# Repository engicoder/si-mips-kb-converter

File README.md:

View this project on [CADLAB.io](https://cadlab.io/project/24614). 

# si-mips-kb-converter
Mainboard replacement for SI version of mips 16-00100 keyboard to convert to USB

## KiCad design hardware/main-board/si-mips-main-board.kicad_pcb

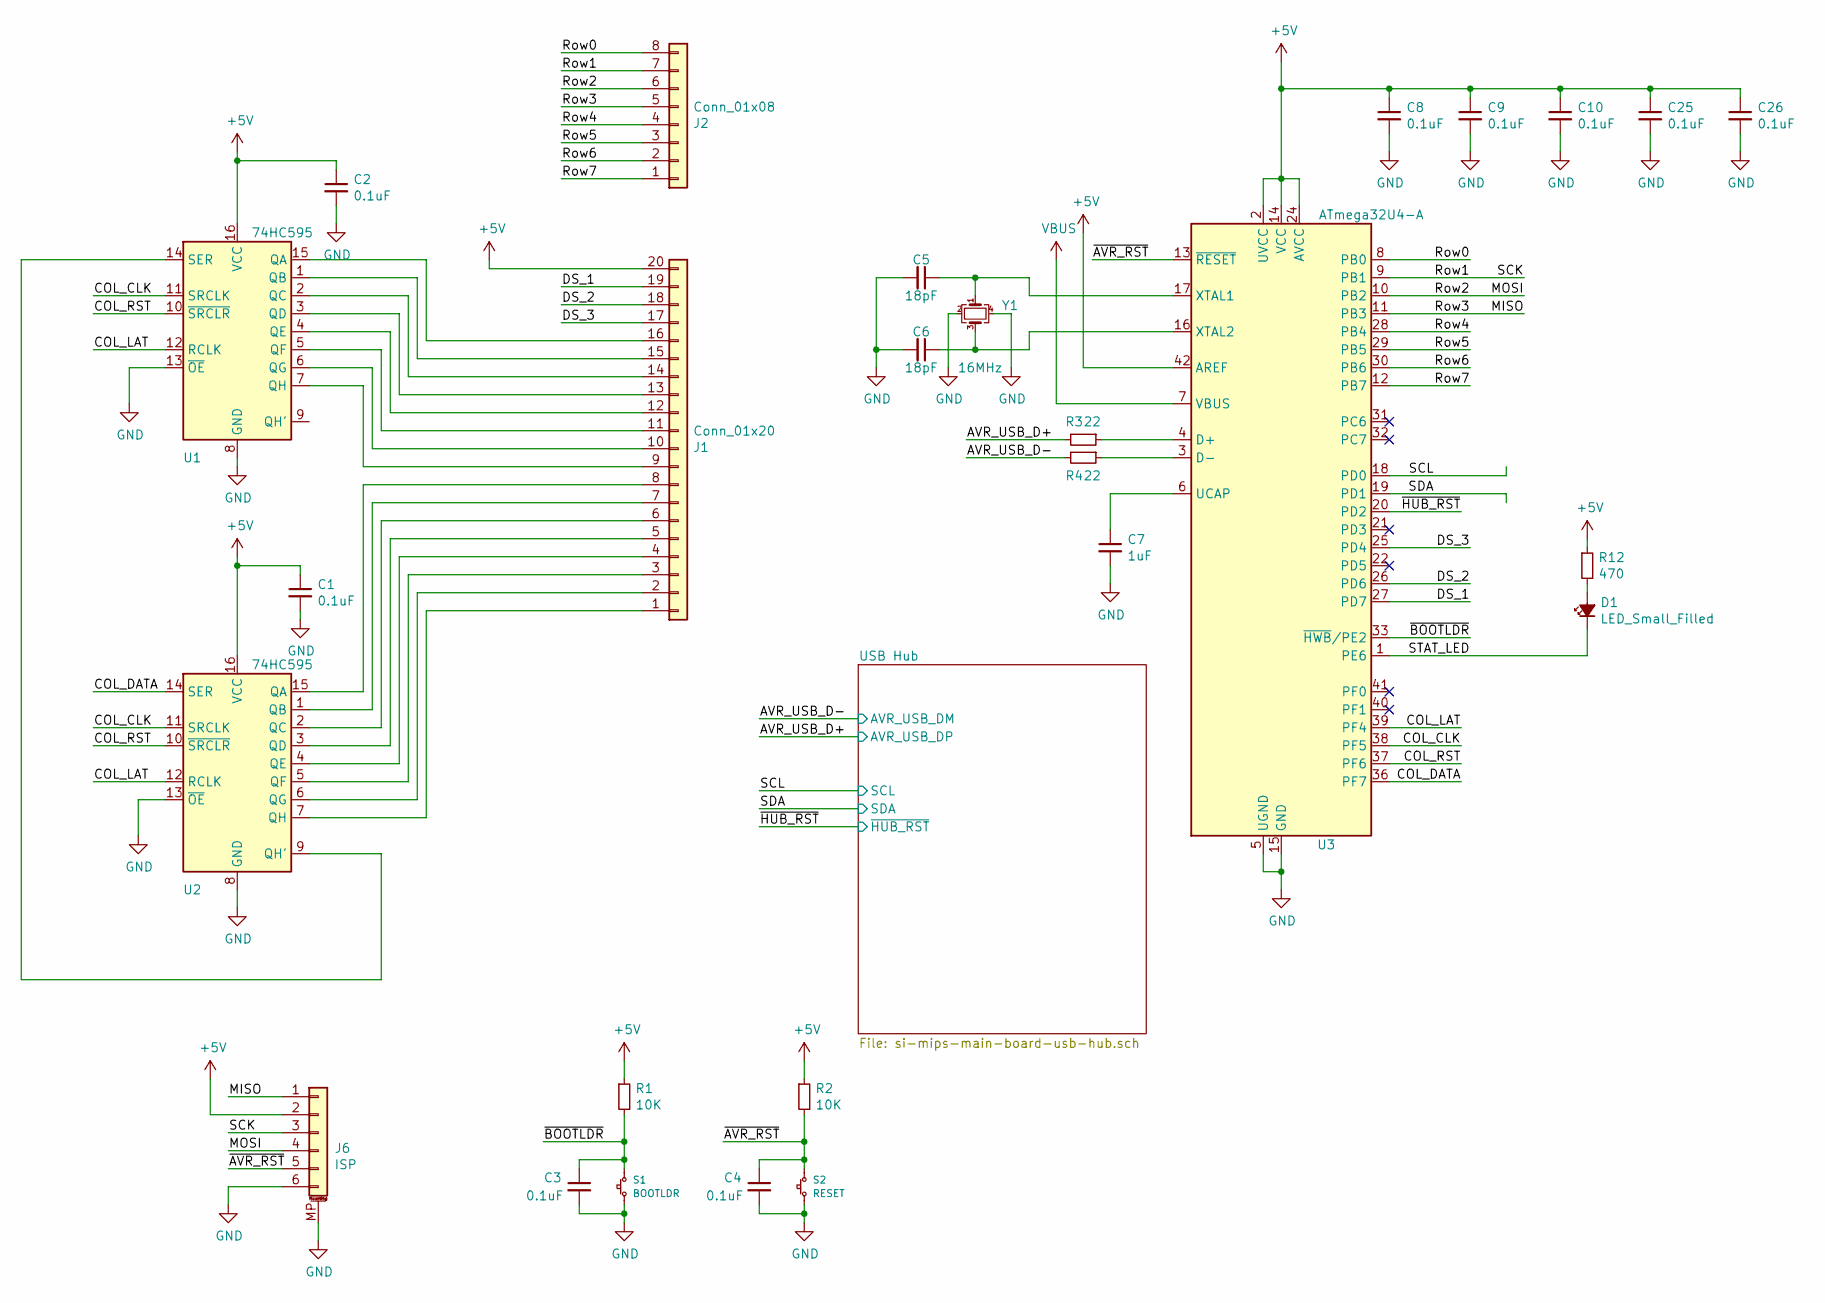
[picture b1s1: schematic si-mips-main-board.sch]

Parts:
C1, C2, C3, C4, C8, C9, C10, C25, C26: 0.1uF; C_0603_1608Metric
C5, C6: 18pF; C_0603_1608Metric
C7: 1uF; C_0603_1608Metric
D1: LED_Small_Filled; LED_0603_1608Metric
J1: Conn_01x20; PinHeader_1x20_P2.54mm_Vertical
J2: Conn_01x08; PinHeader_1x08_P2.54mm_Vertical
J6: ISP; JST_SH_SM06B-SRSS-TB_1x06-1MP_P1.00mm_Horizontal
R1, R2: 10K; R_0603_1608Metric
R3, R4: 22; R_0603_1608Metric
R12: 470; R_0603_1608Metric
S1: BOOTLDR; SW_SPST_Omron_B3FS-101xP
S2: RESET; SW_SPST_Omron_B3FS-101xP
U1, U2: 74HC595; SO-16_3.9x9.9mm_P1.27mm
U3: ATmega32U4-A; TQFP-44_10x10mm_P0.8mm
Y1: 16MHz; Crystal_SMD_3225-4Pin_3.2x2.5mm

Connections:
+5V: C1.1, C2.1, C8.1, C9.1, C10.1, C25.1, C26.1, J1.20, J6.2, R1.1, R2.1, R12.1, U1.16 (VCC), U2.16 (VCC), U3.2 (UVCC), U3.14 (VCC), U3.24 (AVCC), U3.34 (VCC), U3.42 (AREF), U3.44 (AVCC); also elsewhere on the board
/AVR_USB_D+: R3.2; also elsewhere on the board
/AVR_USB_D-: R4.2; also elsewhere on the board
/COL_CLK: U1.11 (SRCLK), U2.11 (SRCLK), U3.38 (PF5)
/COL_DATA: U2.14 (SER), U3.36 (PF7)
/COL_LAT: U1.12 (RCLK), U2.12 (RCLK), U3.39 (PF4)
/COL_RST: U1.10 (~SRCLR), U2.10 (~SRCLR), U3.37 (PF6)
/DS_1: J1.19, U3.27 (PD7)
/DS_2: J1.18, U3.26 (PD6)
/DS_3: J1.17, U3.25 (PD4)
/MISO: J2.5, J6.1, U3.11 (PB3)
/MOSI: J2.6, J6.4, U3.10 (PB2)
/Row0: J2.8, U3.8 (PB0)
/Row1: J2.7, J6.3, U3.9 (PB1)
/Row4: J2.4, U3.28 (PB4)
/Row5: J2.3, U3.29 (PB5)
/Row6: J2.2, U3.30 (PB6)
/Row7: J2.1, U3.12 (PB7)
/SCL: U3.18 (PD0); also elsewhere on the board
/SDA: U3.19 (PD1); also elsewhere on the board
/STAT_LED: D1.1 (K), U3.1 (PE6)
/~AVR_RST: C4.1, J6.5, R2.2, S2.1, U3.13 (~RESET)
/~BOOTLDR: C3.1, R1.2, S1.1, U3.33 (~HWB~/PE2)
/~HUB_RST: U3.20 (PD2); also elsewhere on the board
GND: C1.2, C2.2, C3.2, C4.2, C5.2, C6.2, C7.2, C8.2, C9.2, C10.2, C25.2, C26.2, J6.6, J6.MP (MountPin), S1.2, S2.2, U1.8 (GND), U1.13 (~OE), U2.8 (GND), U2.13 (~OE), U3.5 (UGND), U3.15 (GND), U3.23 (GND), U3.35 (GND), U3.43 (GND), Y1.2, Y1.4; also elsewhere on the board
unnamed: C5.1, U3.17 (XTAL1), Y1.1
unnamed: C6.1, U3.16 (XTAL2), Y1.3
unnamed: C7.1, U3.6 (UCAP)
unnamed: D1.2 (A), R12.2
unnamed: J1.1, U2.7 (QH)
unnamed: J1.2, U2.6 (QG)
unnamed: J1.3, U2.5 (QF)
unnamed: J1.4, U2.4 (QE)
unnamed: J1.5, U2.3 (QD)
unnamed: J1.6, U2.2 (QC)
unnamed: J1.7, U2.1 (QB)
unnamed: J1.8, U2.15 (QA)
unnamed: J1.9, U1.7 (QH)
unnamed: J1.10, U1.6 (QG)
unnamed: J1.11, U1.5 (QF)
unnamed: J1.12, U1.4 (QE)
unnamed: J1.13, U1.3 (QD)
unnamed: J1.14, U1.2 (QC)
unnamed: J1.15, U1.1 (QB)
unnamed: J1.16, U1.15 (QA)
unnamed: R3.1, U3.4 (D+)
unnamed: R4.1, U3.3 (D-)
unnamed: U1.14 (SER), U2.9 (QH')
VBUS: U3.7 (VBUS); also elsewhere on the board

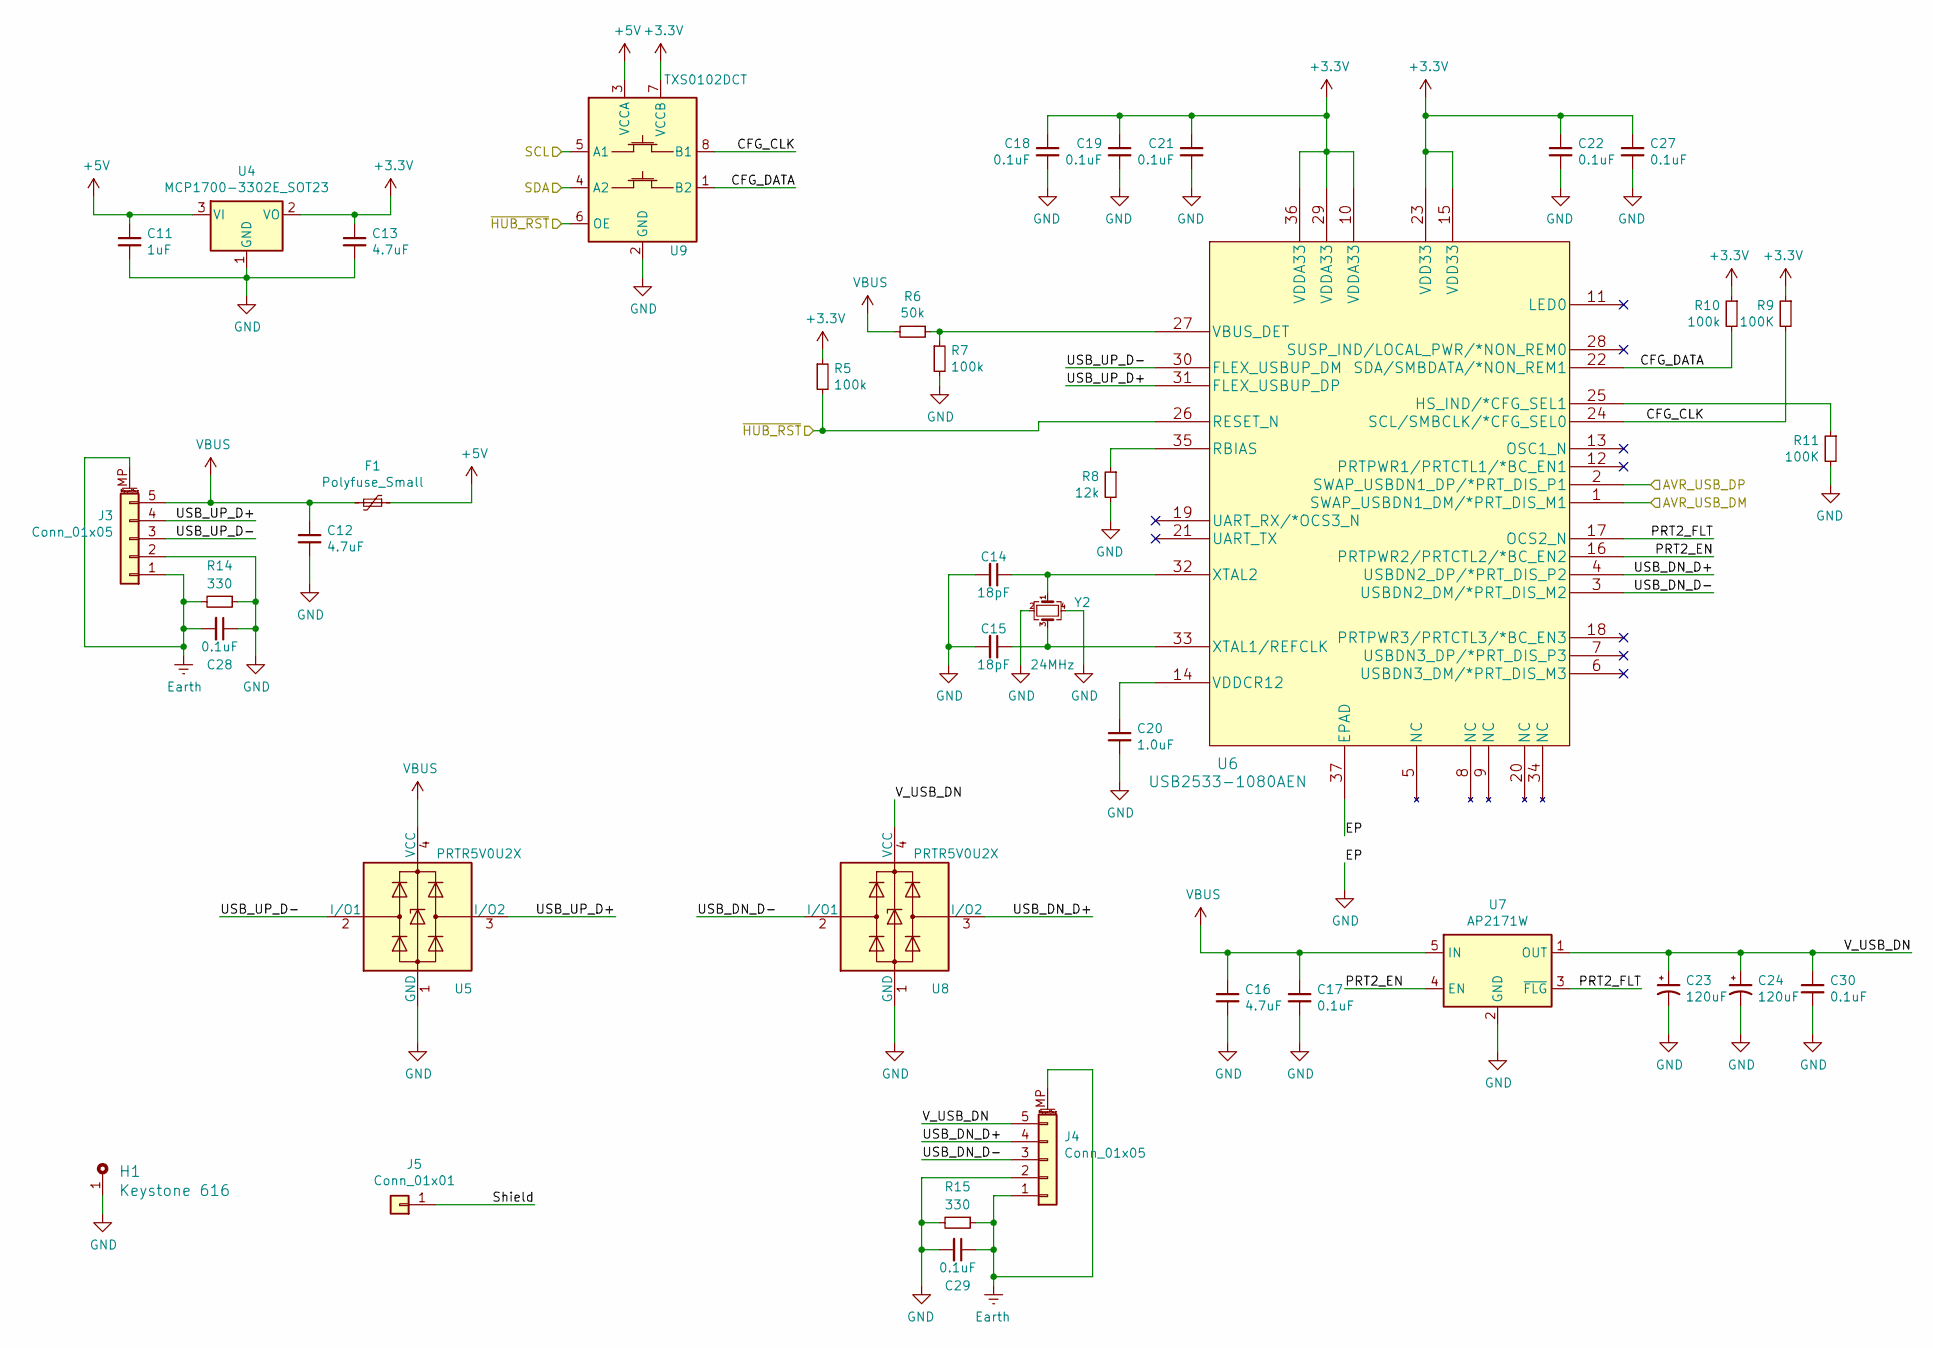
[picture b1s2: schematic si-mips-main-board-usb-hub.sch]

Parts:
C11: 1uF; C_0603_1608Metric
C12, C13, C16: 4.7uF; C_0805_2012Metric
C14, C15: 18pF; C_0603_1608Metric
C17, C18, C19, C21, C22, C27, C28, C29, C30: 0.1uF; C_0603_1608Metric
C20: 1.0uF; C_0603_1608Metric
C23, C24: 120uF; CP_EIA-7343-31_Kemet-D
F1: Polyfuse_Small; Fuse_0805_2012Metric
H1: Keystone 616; MountingHole_3.5mm_Pad_Via
J3, J4: Conn_01x05
J5: Conn_01x01; TestPoint_THTPad_D4.0mm_Drill2.0mm
R5, R7, R10: 100k; R_0603_1608Metric
R6: 50k; R_0603_1608Metric
R8: 12k; R_0603_1608Metric
R9, R11: 100K; R_0603_1608Metric
R14, R15: 330; R_0603_1608Metric
U4: MCP1700-3302E_SOT23; SOT-23
U5, U8: PRTR5V0U2X; SOT-143
U6: USB2533-1080AEN; QFN-36-1EP_6x6mm_P0.5mm_EP3.7x3.7_ThermalVias_0.3mm_drill
U7: AP2171W; SOT-23-5
U9: TXS0102DCT; SSOP-8_2.95x2.8mm_P0.65mm
Y2: 24MHz; Crystal_SMD_2016-4Pin_2.0x1.6mm; MPN XRCGB24M000F2P00R0

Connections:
+3V3: C13.1, C18.1, C19.1, C21.1, C22.1, C27.1, R5.1, R9.1, R10.1, U4.2 (VO), U6.10 (VDDA33), U6.15 (VDD33), U6.23 (VDD33), U6.29 (VDDA33), U6.36 (VDDA33), U9.7 (VCCB)
+5V: C11.1, F1.1, U4.3 (VI), U9.3 (VCCA); also elsewhere on the board
/AVR_USB_D+: U6.2 (SWAP_USBDN1_DP/*PRT_DIS_P1); also elsewhere on the board
/AVR_USB_D-: U6.1 (SWAP_USBDN1_DM/*PRT_DIS_M1); also elsewhere on the board
/SCL: U9.5 (A1); also elsewhere on the board
/SDA: U9.4 (A2); also elsewhere on the board
/USB Hub/CFG_CLK: R9.2, U6.24 (SCL/SMBCLK/*CFG_SEL0), U9.8 (B1)
/USB Hub/CFG_DATA: R10.2, U6.22 (SDA/SMBDATA/*NON_REM1), U9.1 (B2)
/USB Hub/PRT2_EN: U6.16 (PRTPWR2/PRTCTL2/*BC_EN2), U7.4 (EN)
/USB Hub/PRT2_FLT: U6.17 (OCS2_N), U7.3 (~FLG)
/USB Hub/Shield: J5.1
/USB Hub/USB_DN_D+: J4.4, U6.4 (USBDN2_DP/*PRT_DIS_P2), U8.3 (I/O2)
/USB Hub/USB_DN_D-: J4.3, U6.3 (USBDN2_DM/*PRT_DIS_M2), U8.2 (I/O1)
/USB Hub/USB_UP_D+: J3.4, U5.3 (I/O2), U6.31 (FLEX_USBUP_DP)
/USB Hub/USB_UP_D-: J3.3, U5.2 (I/O1), U6.30 (FLEX_USBUP_DM)
/USB Hub/V_USB_DN: C23.1, C24.1, C30.1, J4.5, U7.1 (OUT), U8.4 (VCC)
/~HUB_RST: R5.2, U6.26 (RESET_N), U9.6 (OE); also elsewhere on the board
Earth: C28.2, C29.1, J3.1, J3.MP (MountPin), J4.1, J4.MP (MountPin), R14.2, R15.1
GND: C11.2, C12.2, C13.2, C14.2, C15.2, C16.2, C17.2, C18.2, C19.2, C20.2, C21.2, C22.2, C23.2, C24.2, C27.2, C28.1, C29.2, C30.2, H1.1, J3.2, J4.2, R7.2, R8.2, R11.2, R14.1, R15.2, U4.1 (GND), U5.1 (GND), U6.37 (EPAD), U7.2 (GND), U8.1 (GND), U9.2 (GND), Y2.2, Y2.4; also elsewhere on the board
unnamed: C14.1, U6.32 (XTAL2), Y2.1
unnamed: C15.1, U6.33 (XTAL1/REFCLK), Y2.3
unnamed: C20.1, U6.14 (VDDCR12)
unnamed: R6.1, R7.1, U6.27 (VBUS_DET)
unnamed: R8.1, U6.35 (RBIAS)
unnamed: R11.1, U6.25 (HS_IND/*CFG_SEL1)
VBUS: C12.1, C16.1, C17.1, F1.2, J3.5, R6.2, U5.4 (VCC), U7.5 (IN); also elsewhere on the board

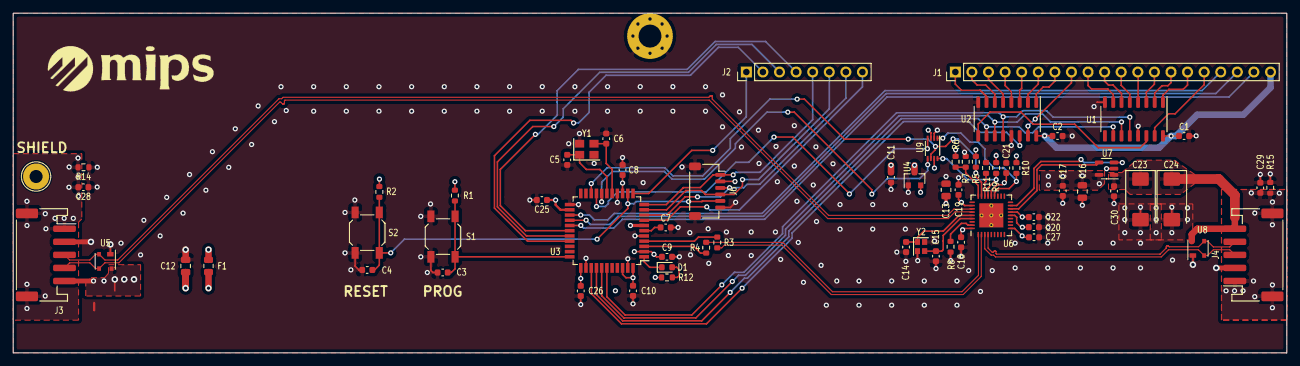
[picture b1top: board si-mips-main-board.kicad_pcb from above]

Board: 4 copper layers, 195.0 x 52.0 mm, 66 parts (0 on the bottom side), 66 nets.

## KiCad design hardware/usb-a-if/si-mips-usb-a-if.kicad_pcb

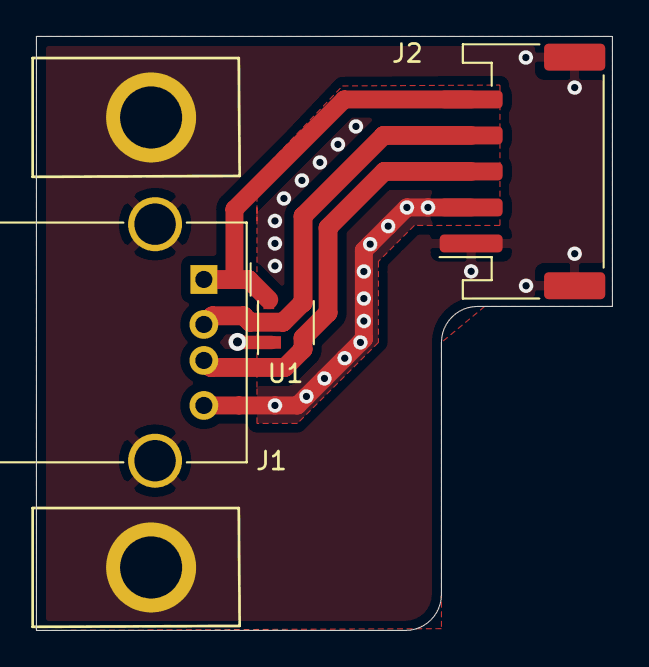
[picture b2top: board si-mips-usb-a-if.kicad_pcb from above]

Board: 2 copper layers, 32.0 x 33.0 mm, 5 parts (0 on the bottom side), 5 nets.

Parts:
H1, H2: keystone-616
J1: USB_A; USB_A_Molex_67643_Horizontal
J2: Conn_01x05_MountingPin; JST_PH_S5B-PH-SM4-TB_1x05-1MP_P2.00mm_Horizontal
U1: PRTR5V0U2X; NXP_SOT143B

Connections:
/D+: J1.3, J2.3, U1.2
/D-: J1.2, J2.4, U1.3
Earth: H1.1, H2.1, J1.5, J2.1, J2.MP, U1.1
GND: J1.4, J2.2
VBUS: J1.1, J2.5, U1.4

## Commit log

2021-08-18 Backlink to CADLAB.io has been added.
